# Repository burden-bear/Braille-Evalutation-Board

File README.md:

# Braille-Evalutation-Board
Adapted from https://hackaday.io/project/191181-electromechanical-refreshable-braille-module

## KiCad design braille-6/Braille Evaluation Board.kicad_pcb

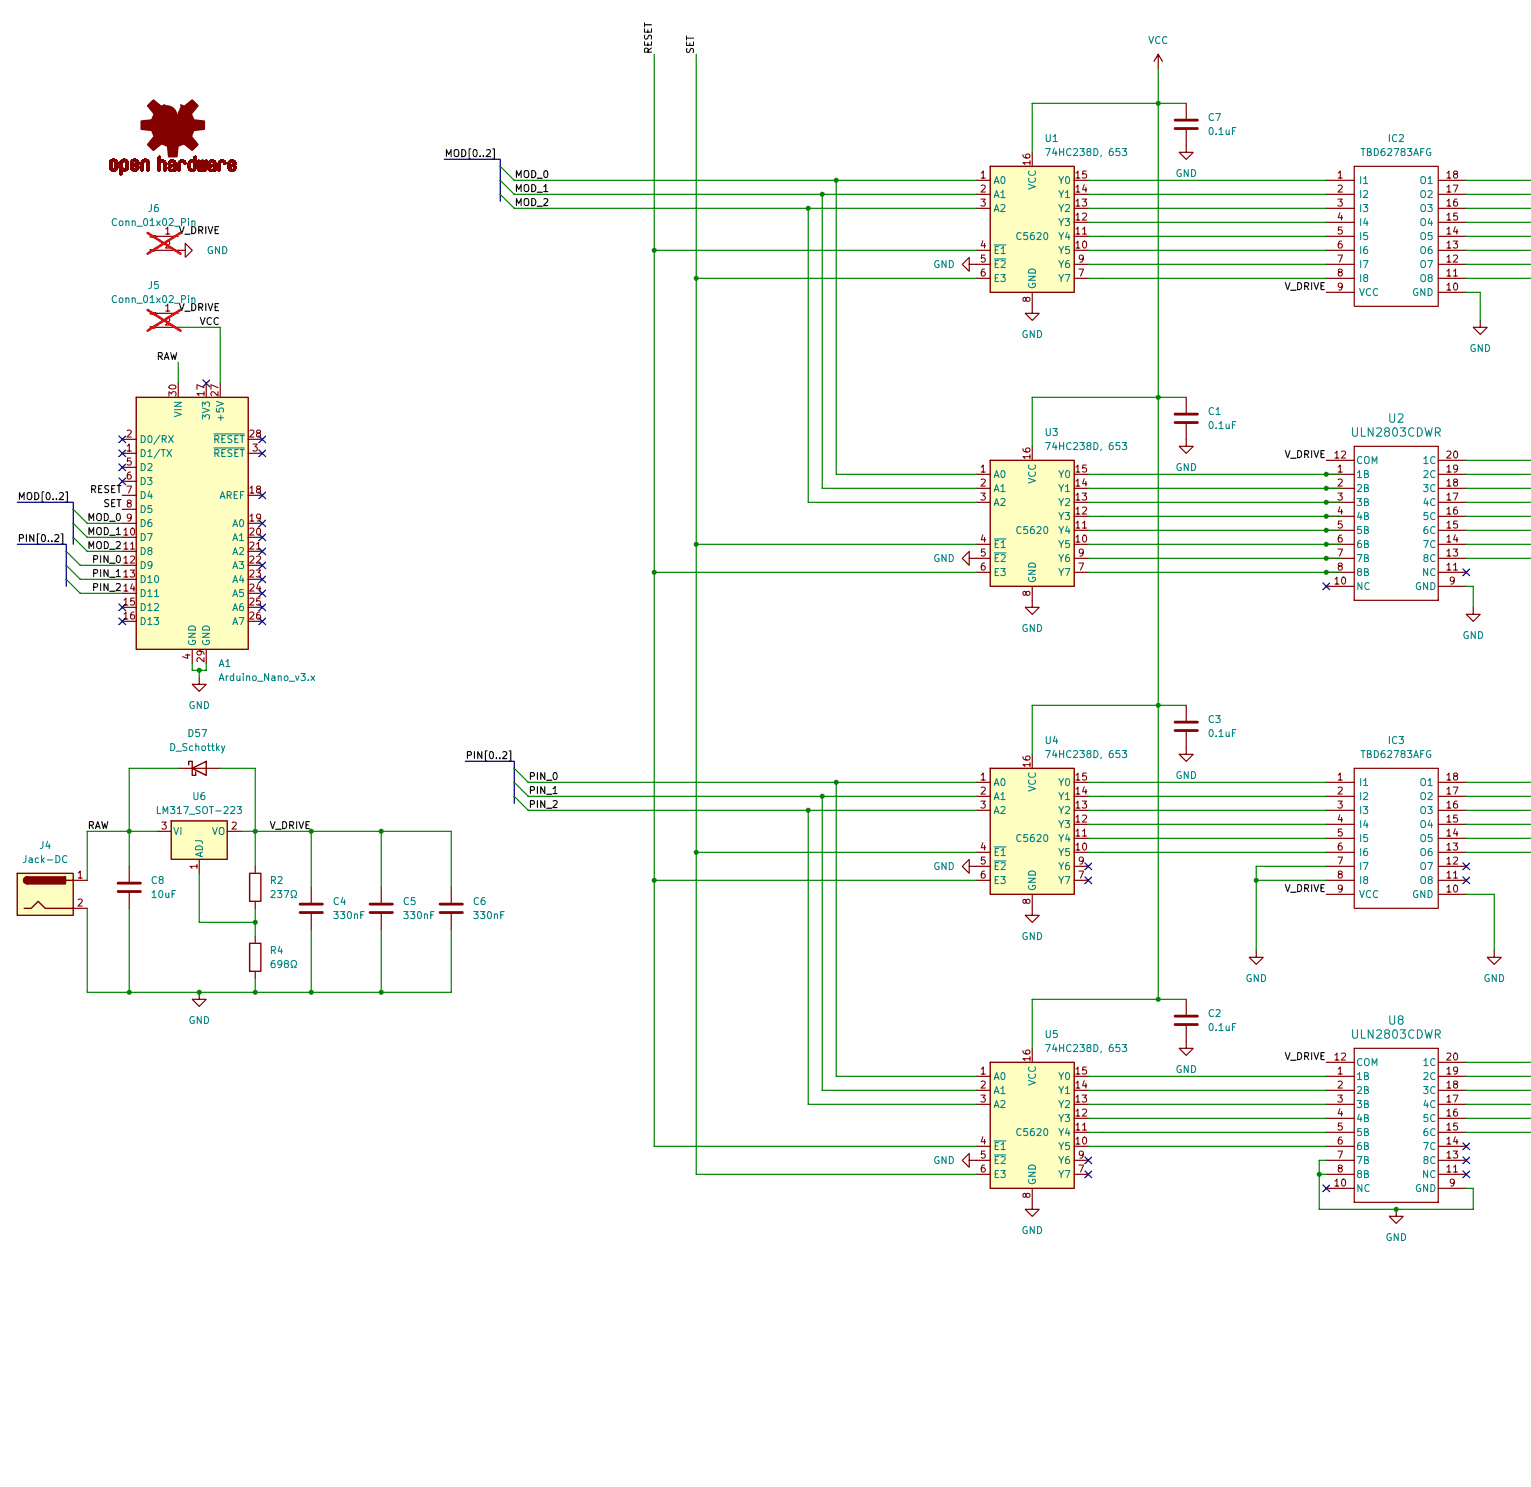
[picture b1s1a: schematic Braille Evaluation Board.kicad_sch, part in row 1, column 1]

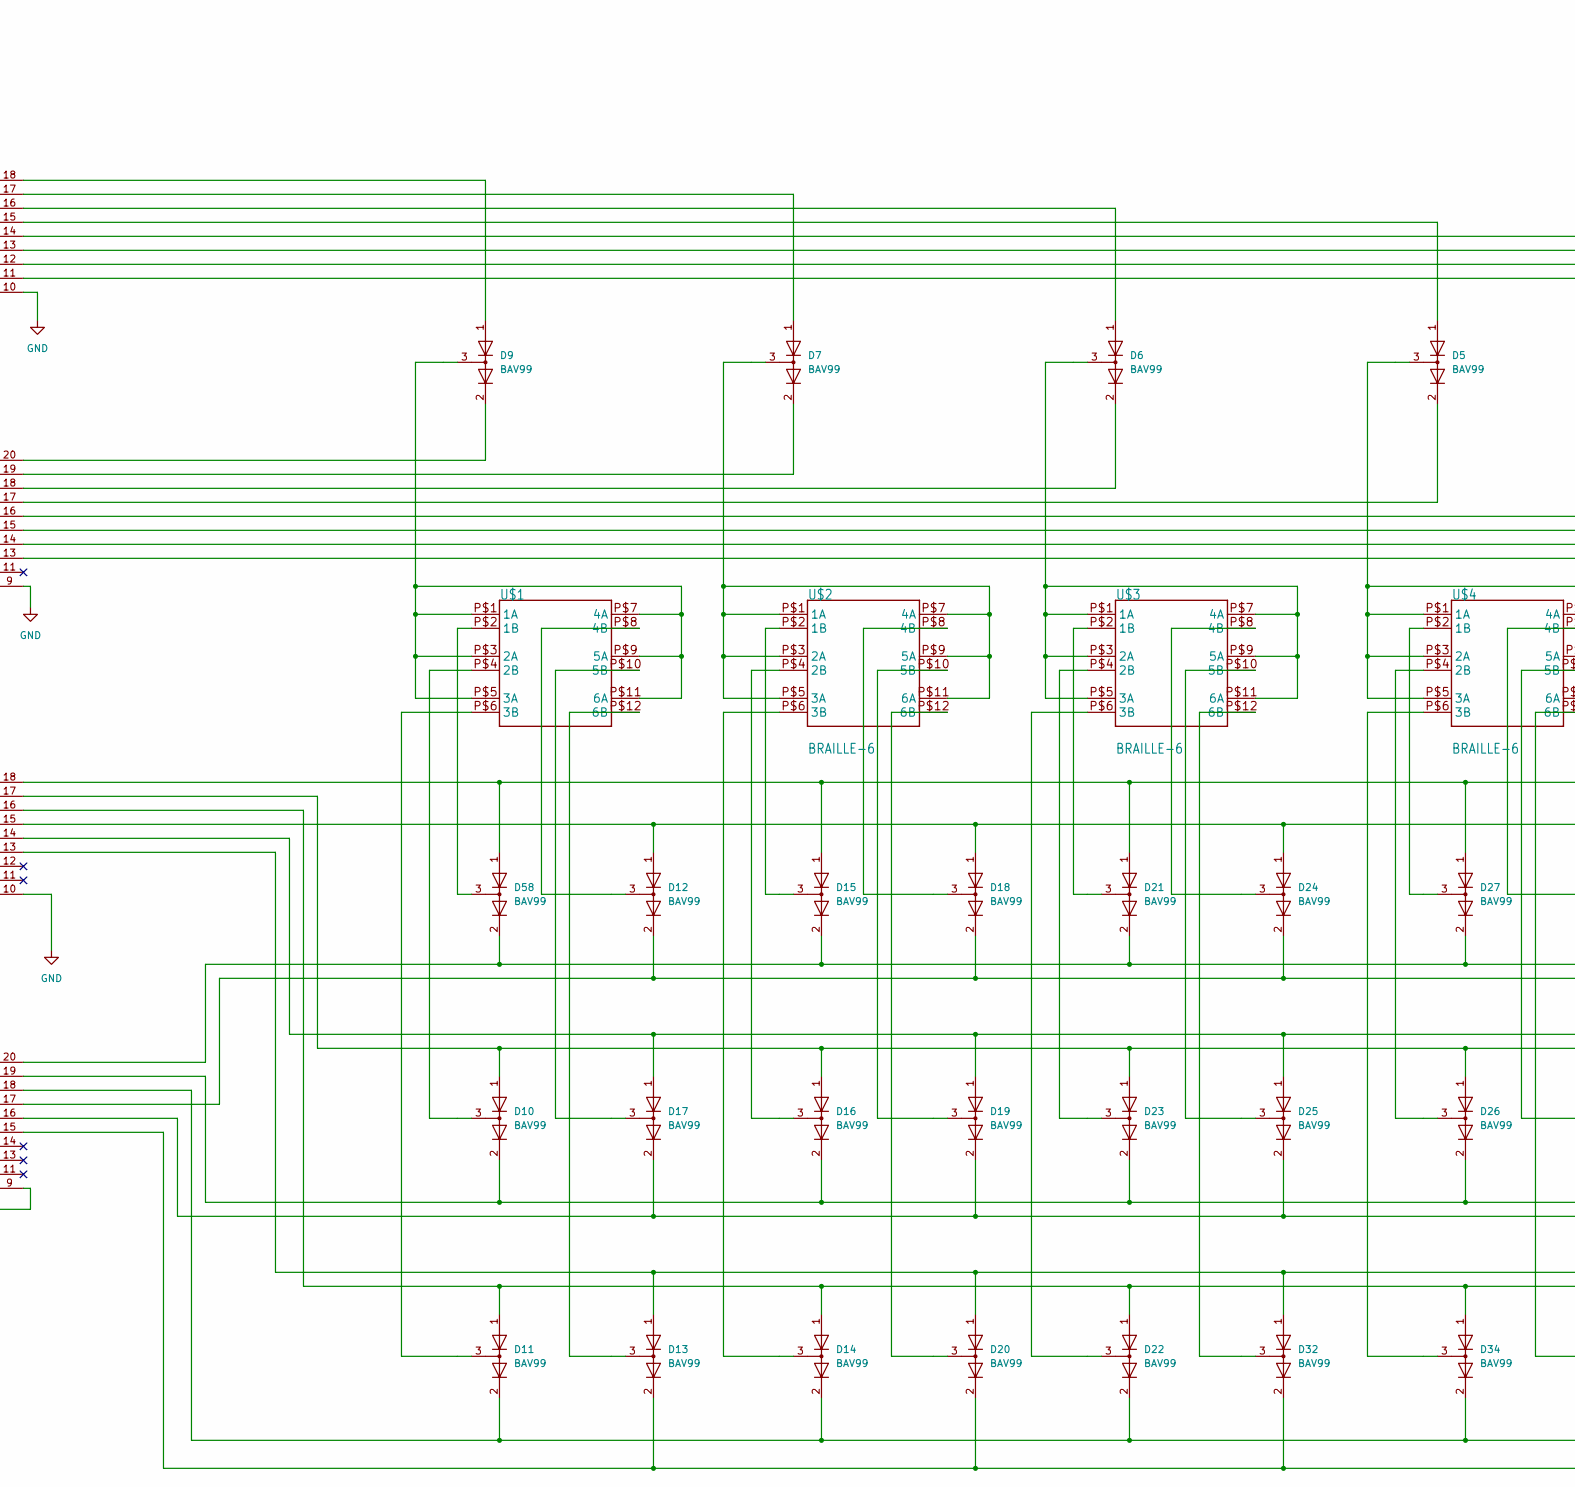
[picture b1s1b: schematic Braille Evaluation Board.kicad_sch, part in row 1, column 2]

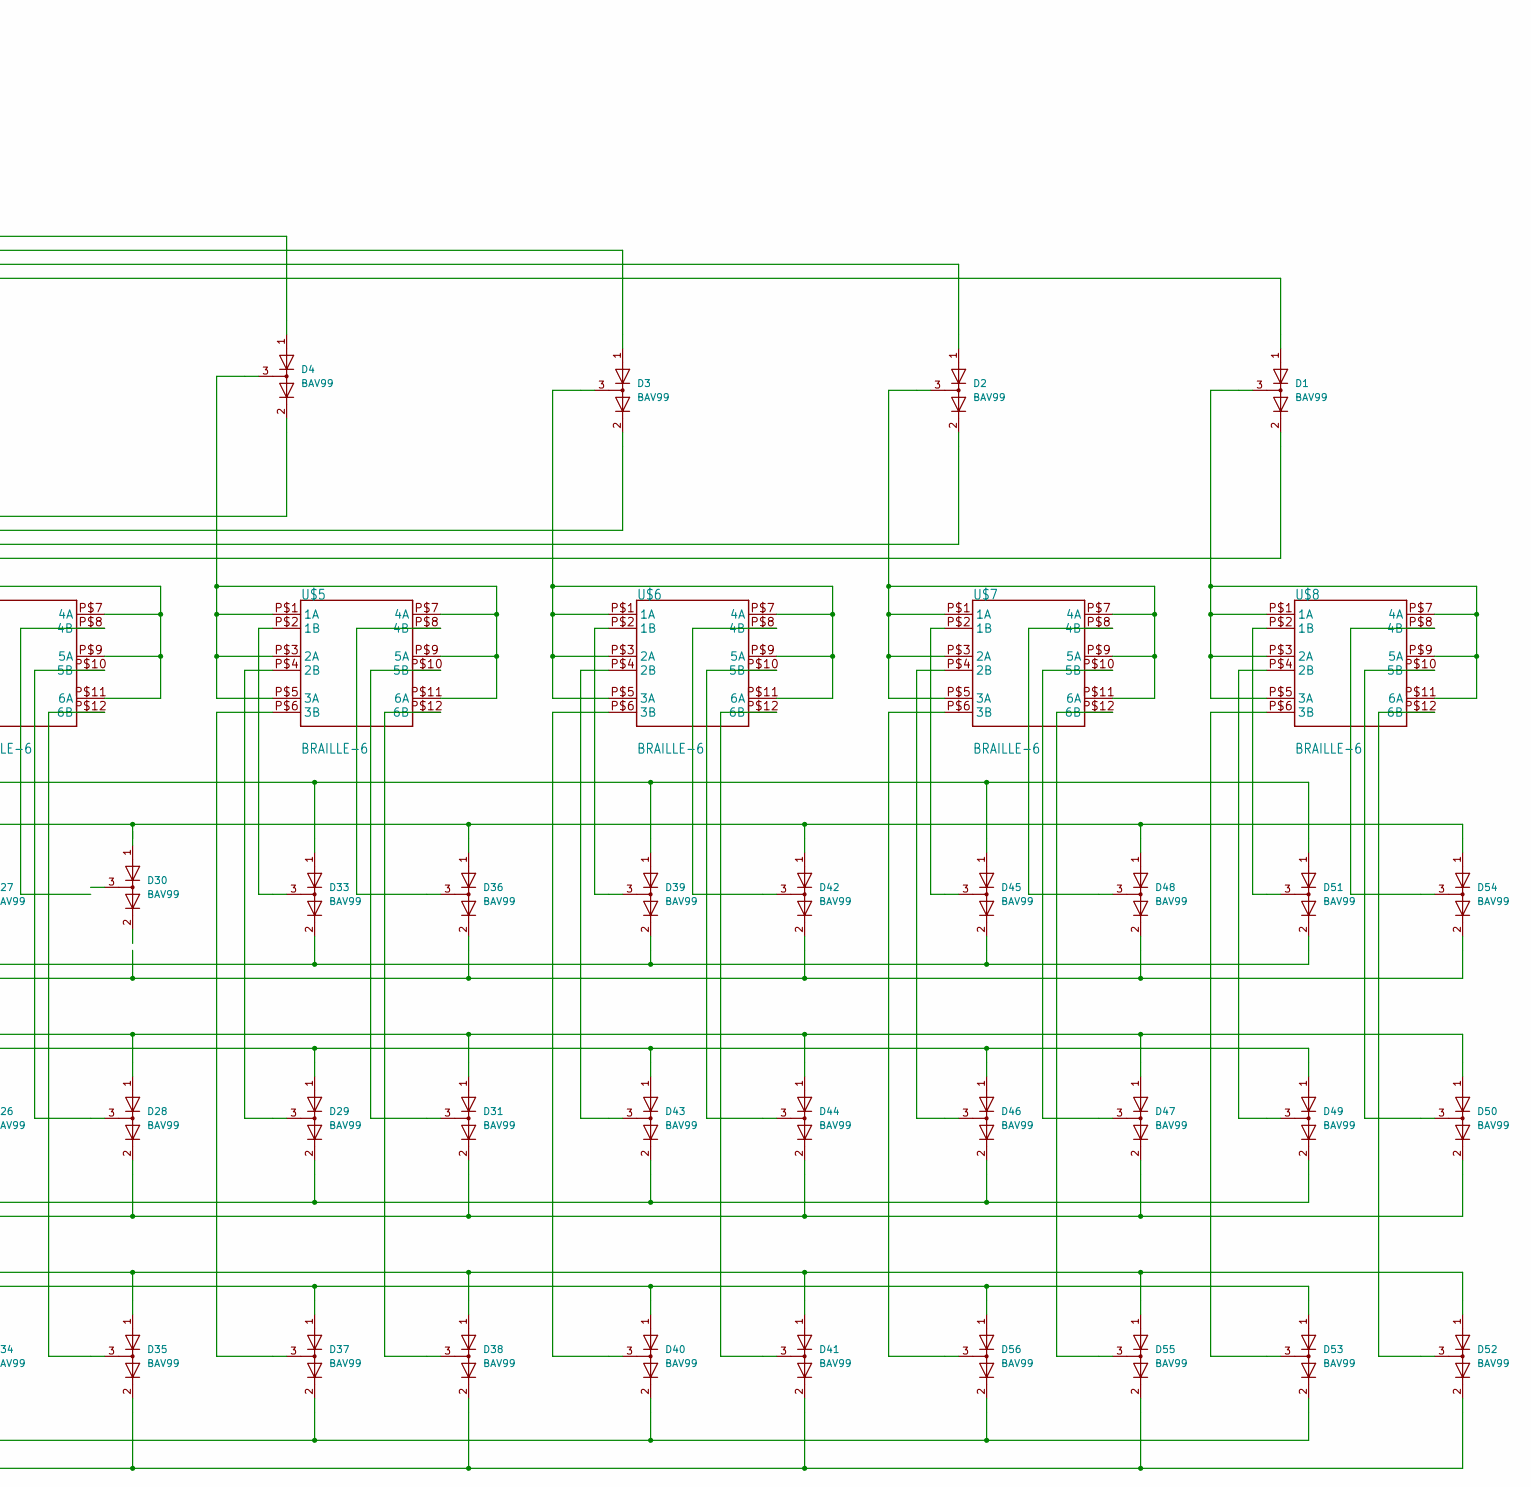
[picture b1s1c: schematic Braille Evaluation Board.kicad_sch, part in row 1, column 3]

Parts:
A1: Arduino_Nano_v3.x; Arduino_Nano
C1, C2, C3, C7: 0.1uF; C_0402_1005Metric; LCSC Part # C71629
C4, C5, C6: 330nF; C_0402_1005Metric; LCSC Part # C913655
C8: 10uF; C_0603_1608Metric; LCSC Part # C92487
D1, D2, D3, D4, D5, D6, D7, D9, D10, D11, D12, D13, D14, D15, D16, D17, D18, D19, D20, D21, D22, D23, D24, D25, D26, D27, D28, D29, D30, D31, D32, D33, D34, D35, D36, D37, D38, D39, D40, D41, D42, D43, D44, D45, D46, D47, D48, D49, D50, D51, D52, D53, D54, D55, D56, D58: BAV99; SOT-23-3; LCSC Part # C7420336
D57: D_Schottky; D_SOD-323; LCSC Part # C177096
IC2, IC3: TBD62783AFG; SOIC-18W_7.5x11.6mm_P1.27mm; Manufacturer_Part_Number TBD62783AFG; Mouser Part Number N/A
J4: Jack-DC; BarrelJack_Kycon_KLDX-0202-xC_Horizontal; LCSC Part # C16214
J5, J6: Conn_01x02_Pin; PinHeader_1x02_P2.54mm_Vertical; not fitted
LOGO1: OSHW-LOGOL-COPPER; OSHW-LOGO-L_COPPER
R2: 237Ω; LED_0603_1608Metric; LCSC Part # C23012
R4: 698Ω; R_0402_1005Metric; LCSC Part # C966739
U1, U3, U4, U5: 74HC238D, 653; SOIC-16_3.9x9.9mm_P1.27mm; LCSC Part # C5620
U2, U8: ULN2803CDWR; DW0020A-MFG; LCSC Part # C7494313
U6: LM317_SOT-223; SOT-223-3_TabPin2; LCSC Part # C51466
U$1, U$2, U$3, U$4, U$5, U$6, U$7, U$8: BRAILLE-6

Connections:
/MOD_0: A1.9 (D6), U1.1 (A0), U3.1 (A0)
/MOD_1: A1.10 (D7), U1.2 (A1), U3.2 (A1)
/MOD_2: A1.11 (D8), U1.3 (A2), U3.3 (A2)
/PIN_0: A1.12 (D9), U4.1 (A0), U5.1 (A0)
/PIN_1: A1.13 (D10), U4.2 (A1), U5.2 (A1)
/PIN_2: A1.14 (D11), U4.3 (A2), U5.3 (A2)
/RAW: A1.30 (VIN), C8.1, D57.1 (K), J4.1, U6.3 (VI)
/RESET: A1.7 (D4), U1.4 (~E1), U3.6 (E3), U4.6 (E3), U5.4 (~E1)
/SET: A1.8 (D5), U1.6 (E3), U3.4 (~E1), U4.4 (~E1), U5.6 (E3)
/V_DRIVE: C4.1, C5.1, C6.1, D57.2 (A), IC2.9 (VCC), IC3.9 (VCC), J5.1, J6.1, R2.1, U2.12 (COM), U6.2 (VO), U8.12 (COM)
GND: A1.4 (GND), A1.29 (GND), C1.2, C2.2, C3.2, C4.2, C5.2, C6.2, C7.2, C8.2, IC2.10 (GND), IC3.7 (I7), IC3.8 (I8), IC3.10 (GND), J4.2, J6.2, R4.2, U1.5 (~E2), U1.8 (GND), U2.9 (GND), U3.5 (~E2), U3.8 (GND), U4.5 (~E2), U4.8 (GND), U5.5 (~E2), U5.8 (GND), U8.7 (7B), U8.8 (8B), U8.9 (GND)
unnamed: D1.2 (A), U2.13 (8C)
unnamed: D2.2 (A), U2.14 (7C)
unnamed: D3.2 (A), U2.15 (6C)
unnamed: D4.2 (A), U2.16 (5C)
unnamed: D5.2 (A), U2.17 (4C)
unnamed: D6.2 (A), U2.18 (3C)
unnamed: D7.2 (A), U2.19 (2C)
unnamed: D9.2 (A), U2.20 (1C)
unnamed: D10.2 (A), D16.2 (A), D23.2 (A), D26.2 (A), D29.2 (A), D43.2 (A), D46.2 (A), D49.2 (A), U8.19 (2C)
unnamed: D11.2 (A), D14.2 (A), D22.2 (A), D34.2 (A), D37.2 (A), D40.2 (A), D53.2 (A), D56.2 (A), U8.18 (3C)
unnamed: D12.2 (A), D18.2 (A), D24.2 (A), D36.2 (A), D42.2 (A), D48.2 (A), D54.2 (A), U8.17 (4C)
unnamed: D13.2 (A), D20.2 (A), D32.2 (A), D35.2 (A), D38.2 (A), D41.2 (A), D52.2 (A), D55.2 (A), U8.15 (6C)
unnamed: D15.2 (A), D21.2 (A), D27.2 (A), D33.2 (A), D39.2 (A), D45.2 (A), D51.2 (A), D58.2 (A), U8.20 (1C)
unnamed: D17.2 (A), D19.2 (A), D25.2 (A), D28.2 (A), D31.2 (A), D44.2 (A), D47.2 (A), D50.2 (A), U8.16 (5C)
unnamed: IC2.1 (I1), U1.15 (Y0)
unnamed: IC2.2 (I2), U1.14 (Y1)
unnamed: IC2.3 (I3), U1.13 (Y2)
unnamed: IC2.4 (I4), U1.12 (Y3)
unnamed: IC2.5 (I5), U1.11 (Y4)
unnamed: IC2.6 (I6), U1.10 (Y5)
unnamed: IC2.7 (I7), U1.9 (Y6)
unnamed: IC2.8 (I8), U1.7 (Y7)
unnamed: D9.1 (K), IC2.18 (O1)
unnamed: D7.1 (K), IC2.17 (O2)
unnamed: D6.1 (K), IC2.16 (O3)
unnamed: D5.1 (K), IC2.15 (O4)
unnamed: D4.1 (K), IC2.14 (O5)
unnamed: D3.1 (K), IC2.13 (O6)
unnamed: D2.1 (K), IC2.12 (O7)
unnamed: D1.1 (K), IC2.11 (O8)
unnamed: IC3.1 (I1), U4.15 (Y0)
unnamed: IC3.2 (I2), U4.14 (Y1)
unnamed: IC3.3 (I3), U4.13 (Y2)
unnamed: IC3.4 (I4), U4.12 (Y3)
unnamed: IC3.5 (I5), U4.11 (Y4)
unnamed: IC3.6 (I6), U4.10 (Y5)
unnamed: D15.1 (K), D21.1 (K), D27.1 (K), D33.1 (K), D39.1 (K), D45.1 (K), D51.1 (K), D58.1 (K), IC3.18 (O1)
unnamed: D10.1 (K), D16.1 (K), D23.1 (K), D26.1 (K), D29.1 (K), D43.1 (K), D46.1 (K), D49.1 (K), IC3.17 (O2)
unnamed: D11.1 (K), D14.1 (K), D22.1 (K), D34.1 (K), D37.1 (K), D40.1 (K), D53.1 (K), D56.1 (K), IC3.16 (O3)
unnamed: D12.1 (K), D18.1 (K), D24.1 (K), D36.1 (K), D42.1 (K), D48.1 (K), D54.1 (K), IC3.15 (O4)
unnamed: D17.1 (K), D19.1 (K), D25.1 (K), D28.1 (K), D31.1 (K), D44.1 (K), D47.1 (K), D50.1 (K), IC3.14 (O5)
unnamed: D13.1 (K), D20.1 (K), D32.1 (K), D35.1 (K), D38.1 (K), D41.1 (K), D52.1 (K), D55.1 (K), IC3.13 (O6)
unnamed: U2.1 (1B), U3.15 (Y0)
unnamed: U2.2 (2B), U3.14 (Y1)
unnamed: U2.3 (3B), U3.13 (Y2)
unnamed: U2.4 (4B), U3.12 (Y3)
unnamed: U2.5 (5B), U3.11 (Y4)
unnamed: U2.6 (6B), U3.10 (Y5)
unnamed: U2.7 (7B), U3.9 (Y6)
unnamed: U2.8 (8B), U3.7 (Y7)
unnamed: U5.15 (Y0), U8.1 (1B)
unnamed: U5.14 (Y1), U8.2 (2B)
unnamed: U5.13 (Y2), U8.3 (3B)
unnamed: U5.12 (Y3), U8.4 (4B)
unnamed: U5.11 (Y4), U8.5 (5B)
unnamed: U5.10 (Y5), U8.6 (6B)
unnamed: R2.2, R4.1, U6.1 (ADJ)
unnamed: D9.3 (K), U$1.P$1 (1A), U$1.P$3 (2A), U$1.P$5 (3A), U$1.P$7 (4A), U$1.P$9 (5A), U$1.P$11 (6A)
unnamed: D58.3 (K), U$1.P$2 (1B)
unnamed: D10.3 (K), U$1.P$4 (2B)
unnamed: D11.3 (K), U$1.P$6 (3B)
unnamed: D12.3 (K), U$1.P$8 (4B)
unnamed: D17.3 (K), U$1.P$10 (5B)
unnamed: D13.3 (K), U$1.P$12 (6B)
unnamed: D7.3 (K), U$2.P$1 (1A), U$2.P$3 (2A), U$2.P$5 (3A), U$2.P$7 (4A), U$2.P$9 (5A), U$2.P$11 (6A)
unnamed: D15.3 (K), U$2.P$2 (1B)
unnamed: D16.3 (K), U$2.P$4 (2B)
unnamed: D14.3 (K), U$2.P$6 (3B)
unnamed: D18.3 (K), U$2.P$8 (4B)
unnamed: D19.3 (K), U$2.P$10 (5B)
unnamed: D20.3 (K), U$2.P$12 (6B)
unnamed: D6.3 (K), U$3.P$1 (1A), U$3.P$3 (2A), U$3.P$5 (3A), U$3.P$7 (4A), U$3.P$9 (5A), U$3.P$11 (6A)
unnamed: D21.3 (K), U$3.P$2 (1B)
unnamed: D23.3 (K), U$3.P$4 (2B)
unnamed: D22.3 (K), U$3.P$6 (3B)
unnamed: D24.3 (K), U$3.P$8 (4B)
unnamed: D25.3 (K), U$3.P$10 (5B)
unnamed: D32.3 (K), U$3.P$12 (6B)
unnamed: D5.3 (K), U$4.P$1 (1A), U$4.P$3 (2A), U$4.P$5 (3A), U$4.P$7 (4A), U$4.P$9 (5A), U$4.P$11 (6A)
unnamed: D27.3 (K), U$4.P$2 (1B)
unnamed: D26.3 (K), U$4.P$4 (2B)
unnamed: D34.3 (K), U$4.P$6 (3B)
unnamed: D28.3 (K), U$4.P$10 (5B)
unnamed: D35.3 (K), U$4.P$12 (6B)
unnamed: D4.3 (K), U$5.P$1 (1A), U$5.P$3 (2A), U$5.P$5 (3A), U$5.P$7 (4A), U$5.P$9 (5A), U$5.P$11 (6A)
unnamed: D33.3 (K), U$5.P$2 (1B)
unnamed: D29.3 (K), U$5.P$4 (2B)
unnamed: D37.3 (K), U$5.P$6 (3B)
unnamed: D36.3 (K), U$5.P$8 (4B)
unnamed: D31.3 (K), U$5.P$10 (5B)
unnamed: D38.3 (K), U$5.P$12 (6B)
unnamed: D3.3 (K), U$6.P$1 (1A), U$6.P$3 (2A), U$6.P$5 (3A), U$6.P$7 (4A), U$6.P$9 (5A), U$6.P$11 (6A)
unnamed: D39.3 (K), U$6.P$2 (1B)
unnamed: D43.3 (K), U$6.P$4 (2B)
unnamed: D40.3 (K), U$6.P$6 (3B)
unnamed: D42.3 (K), U$6.P$8 (4B)
unnamed: D44.3 (K), U$6.P$10 (5B)
unnamed: D41.3 (K), U$6.P$12 (6B)
unnamed: D2.3 (K), U$7.P$1 (1A), U$7.P$3 (2A), U$7.P$5 (3A), U$7.P$7 (4A), U$7.P$9 (5A), U$7.P$11 (6A)
unnamed: D45.3 (K), U$7.P$2 (1B)
unnamed: D46.3 (K), U$7.P$4 (2B)
unnamed: D56.3 (K), U$7.P$6 (3B)
unnamed: D48.3 (K), U$7.P$8 (4B)
unnamed: D47.3 (K), U$7.P$10 (5B)
unnamed: D55.3 (K), U$7.P$12 (6B)
unnamed: D1.3 (K), U$8.P$1 (1A), U$8.P$3 (2A), U$8.P$5 (3A), U$8.P$7 (4A), U$8.P$9 (5A), U$8.P$11 (6A)
unnamed: D51.3 (K), U$8.P$2 (1B)
unnamed: D49.3 (K), U$8.P$4 (2B)
unnamed: D53.3 (K), U$8.P$6 (3B)
unnamed: D54.3 (K), U$8.P$8 (4B)
unnamed: D50.3 (K), U$8.P$10 (5B)
unnamed: D52.3 (K), U$8.P$12 (6B)
VCC: A1.27 (+5V), C1.1, C2.1, C3.1, C7.1, J5.2, U1.16 (VCC), U3.16 (VCC), U4.16 (VCC), U5.16 (VCC)

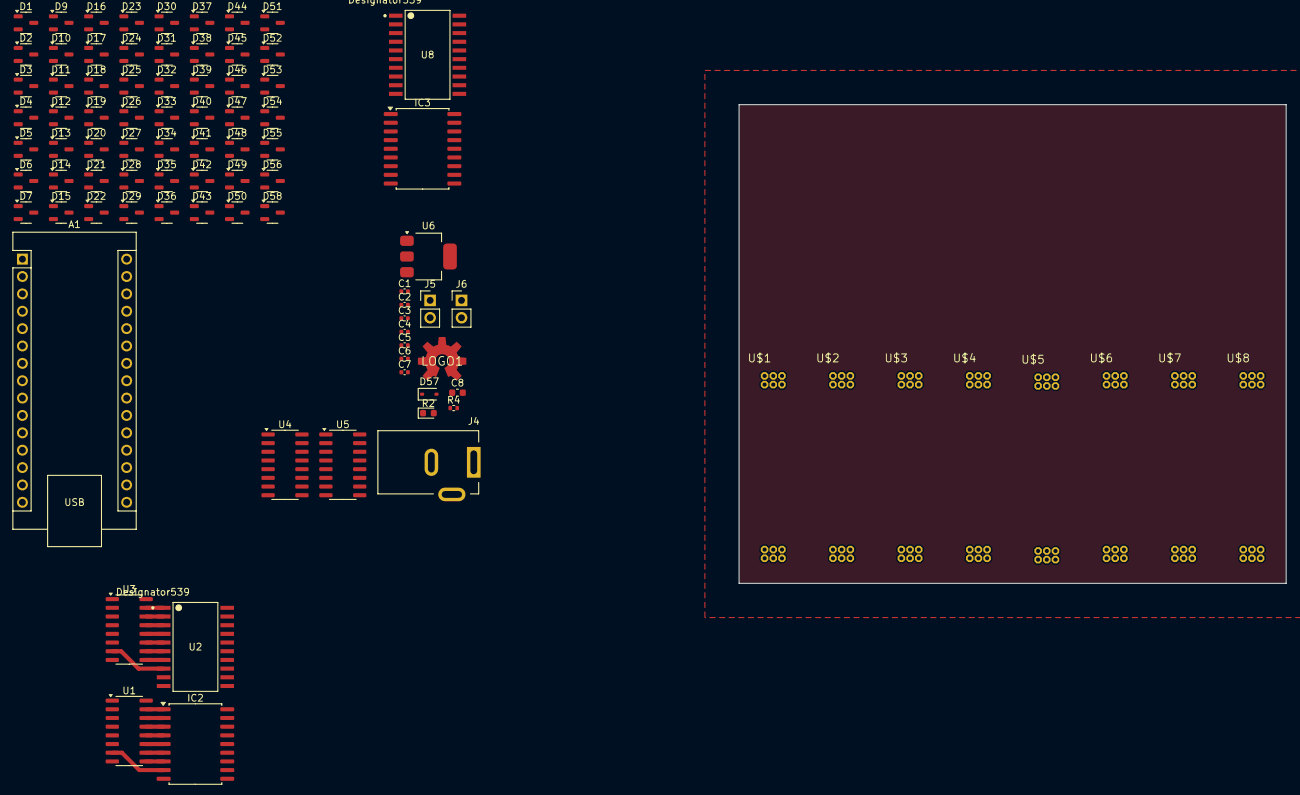
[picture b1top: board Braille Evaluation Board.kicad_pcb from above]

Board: 4 copper layers, 80.0 x 70.0 mm, 89 parts (0 on the bottom side), 124 nets.
